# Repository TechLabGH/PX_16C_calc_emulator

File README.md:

# PX_16C_calc_emulator
all credits go to [paxer.net/voyager/](https://paxer.net/voyager/)

This is great project and useful tool for programmers. I personally prefer that over any software emulator.

Respository is for anybody who would like to COPY of one orderred from developer. This is only partially "open" project. Developer provides schematic and firmware. There is no source code available. Also, Atmega, you are ordering is pre-loaded with flash required to work.

I only re-drafted PCB using SMD componnents (no buzzer due to smaler size). You still would order original kit (let author be paid for his effort) to download flash dump for your copies.

## [Schematic](https://github.com/TechLabGH/PX_16C_calc_emulator/blob/main/HP%2016C%20Pocket.pdf)

Parts:
* [ATMEGA328-AUR](https://www.mouser.com/ProductDetail/556-ATMEGA328-AUR)
* [Crystal](https://www.mouser.com/ProductDetail/710-830003000)
* [Battery Holder](https://www.mouser.com/ProductDetail/12BH002-GR)
* 6x6 Tactile Switches - select high to match your project
* 10ohm / 10Kohm / 2 x 0.1uF - 0603 size
* [Reset button](https://www.mouser.com/ProductDetail/Wurth-Elektronik/431181015816?qs=wr8lucFkNMWQBPdjQ%252B9NsA%3D%3D) - not really needed if your programmer has reset signal.
* [Screen](https://www.aliexpress.us/item/2255800684095628.html?spm=a2g0o.order_list.order_list_main.11.55771802Im1IZ1&gatewayAdapt=glo2usa) - any 2" 192X64 Graphic Matrix LCD Module Display Screen 3.3V - UC1609C would fit. Make sure to buy 3.3V version. Window in top board is made for display's version without metal cover.

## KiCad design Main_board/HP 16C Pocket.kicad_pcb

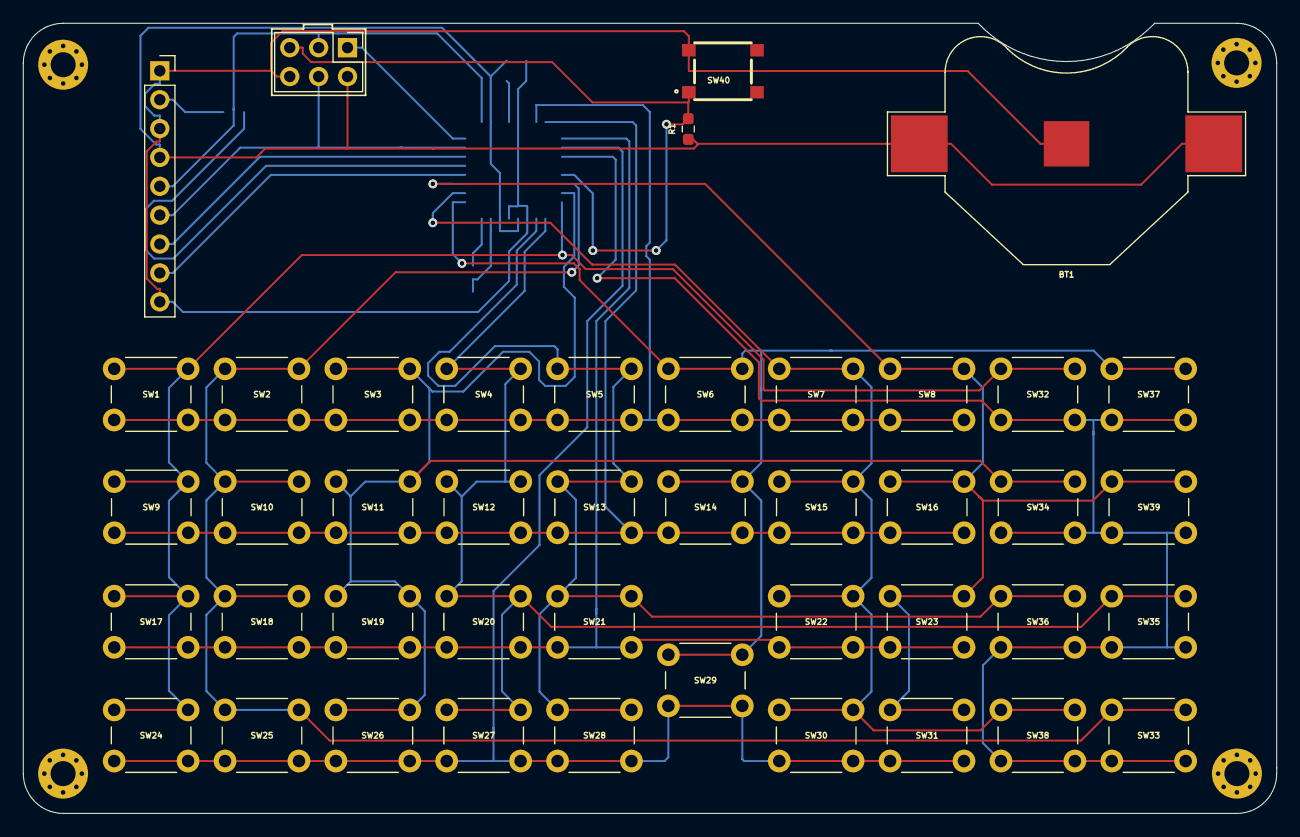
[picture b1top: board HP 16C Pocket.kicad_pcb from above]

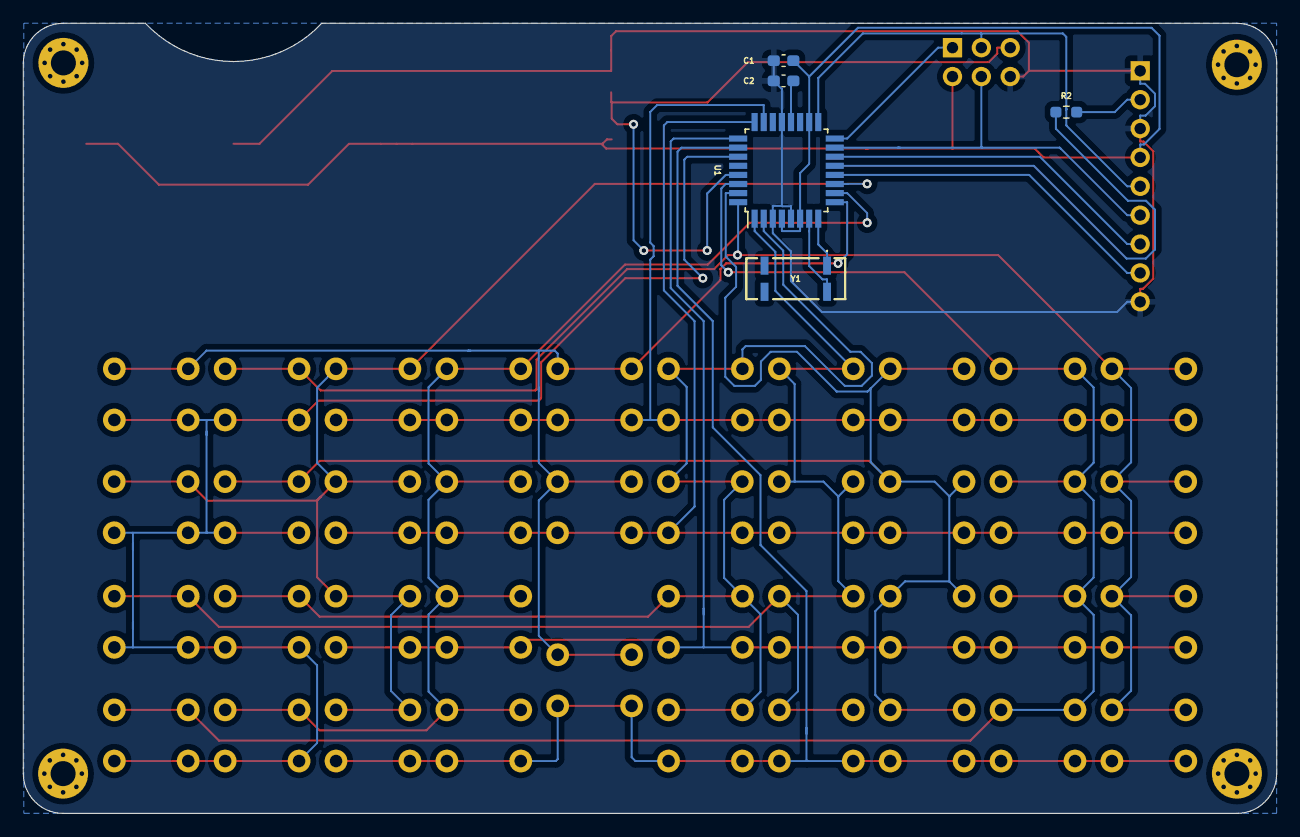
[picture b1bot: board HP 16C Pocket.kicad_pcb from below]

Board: 2 copper layers, 110.2 x 69.5 mm, 53 parts (5 on the bottom side), 26 nets.

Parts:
BT1: Battery; BatteryHolder_Multicomp_BC-2001_1x2032
C1, C2: 0.1uF; C_0603_1608Metric_Pad1.08x0.95mm_HandSolder
H1, H2, H3, H4: MountingHole; MountingHole_2.2mm_M2_Pad_Via
J1: 192X64 LCD; PinSocket_1x09_P2.54mm_Vertical
J2: PRGM; PinHeader_2x03_P2.54mm_Vertical
R1: 10K; R_0603_1608Metric_Pad0.98x0.95mm_HandSolder
R2: 10; R_0603_1608Metric_Pad0.98x0.95mm_HandSolder
SW1, SW2, SW3, SW4, SW5, SW6, SW7, SW8, SW9, SW10, SW11, SW12, SW13, SW14, SW15, SW16, SW17, SW18, SW19, SW20, SW21, SW22, SW23, SW24, SW25, SW26, SW27, SW28, SW29, SW30, SW31, SW32, SW33, SW34, SW35, SW36, SW37, SW38, SW39: SW_Push_Dual_x2; SW_PUSH_6mm
SW40: RST; 431181015816
U1: ATmega328-A; TQFP-32_7x7mm_P0.8mm
Y1: 830003000

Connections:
COL_1: SW2.1 (C), SW10.1 (C), SW18.1 (C), SW25.1 (C), SW33.1 (C), U1.30 (PD0)
COL_2: SW3.1 (C), SW11.1 (C), SW19.1 (C), SW26.1 (C), SW34.1 (C), U1.31 (PD1)
COL_3: SW4.1 (C), SW12.1 (C), SW20.1 (C), SW27.1 (C), SW35.1 (C), U1.1 (PD3)
COL_4: SW5.1 (C), SW13.1 (C), SW21.1 (C), SW28.1 (C), SW36.1 (C), U1.2 (PD4)
COL_5: SW6.1 (C), SW14.1 (C), SW29.1 (C), SW37.1 (C), U1.9 (PD5)
COL_6: SW7.1 (C), SW15.1 (C), SW22.1 (C), SW30.1 (C), SW38.1 (C), U1.10 (PD6)
COL_7: SW8.1 (C), SW16.1 (C), SW23.1 (C), SW31.1 (C), SW39.1 (C), U1.11 (PD7)
COL_IN: SW1.1 (C), SW9.1 (C), SW17.1 (C), SW24.1 (C), SW32.1 (C), U1.32 (PD2)
DISP_LED_PB0: R2.1, U1.13 (PB1)
DISP_MISO: J2.1, U1.16 (PB4)
DISP_MOSI: J1.6, J2.4, U1.15 (PB3)
DISP_RS: J1.8, U1.12 (PB0)
DISP_RST: J1.7, U1.14 (PB2)
DISP_SCK: J1.5, J2.3, U1.17 (PB5)
GND: BT1.2 (-), C1.2, C2.2, J1.1, J1.3, J1.9, J2.6, SW40.2 (D), U1.3 (GND), U1.5 (GND), U1.21 (GND)
unnamed: J1.2, R2.2
unnamed: C2.1, U1.20 (AREF)
unnamed: U1.7 (XTAL1/PB6), Y1.4 (CRYSTAL__2)
unnamed: U1.8 (XTAL2/PB7), Y1.1 (CRYSTAL__1)
ROW_0: SW1.2 (D), SW2.2 (D), SW3.2 (D), SW4.2 (D), SW5.2 (D), SW6.2 (D), SW7.2 (D), SW8.2 (D), U1.23 (PC0)
ROW_1: SW9.2 (D), SW10.2 (D), SW11.2 (D), SW12.2 (D), SW13.2 (D), SW14.2 (D), SW15.2 (D), SW16.2 (D), U1.24 (PC1)
ROW_2: SW17.2 (D), SW18.2 (D), SW19.2 (D), SW20.2 (D), SW21.2 (D), SW22.2 (D), SW23.2 (D), U1.25 (PC2)
ROW_3: SW24.2 (D), SW25.2 (D), SW26.2 (D), SW27.2 (D), SW28.2 (D), SW29.2 (D), SW30.2 (D), SW31.2 (D), U1.26 (PC3)
ROW_4: SW32.2 (D), SW33.2 (D), SW34.2 (D), SW35.2 (D), SW36.2 (D), SW37.2 (D), SW38.2 (D), SW39.2 (D), U1.27 (PC4)
RST: J2.5, R1.2, SW40.1 (C), U1.29 (~RESET/PC6)
VCC: BT1.1 (+), C1.1, J1.4, J2.2, R1.1, U1.4 (VCC), U1.6 (VCC), U1.18 (AVCC)
